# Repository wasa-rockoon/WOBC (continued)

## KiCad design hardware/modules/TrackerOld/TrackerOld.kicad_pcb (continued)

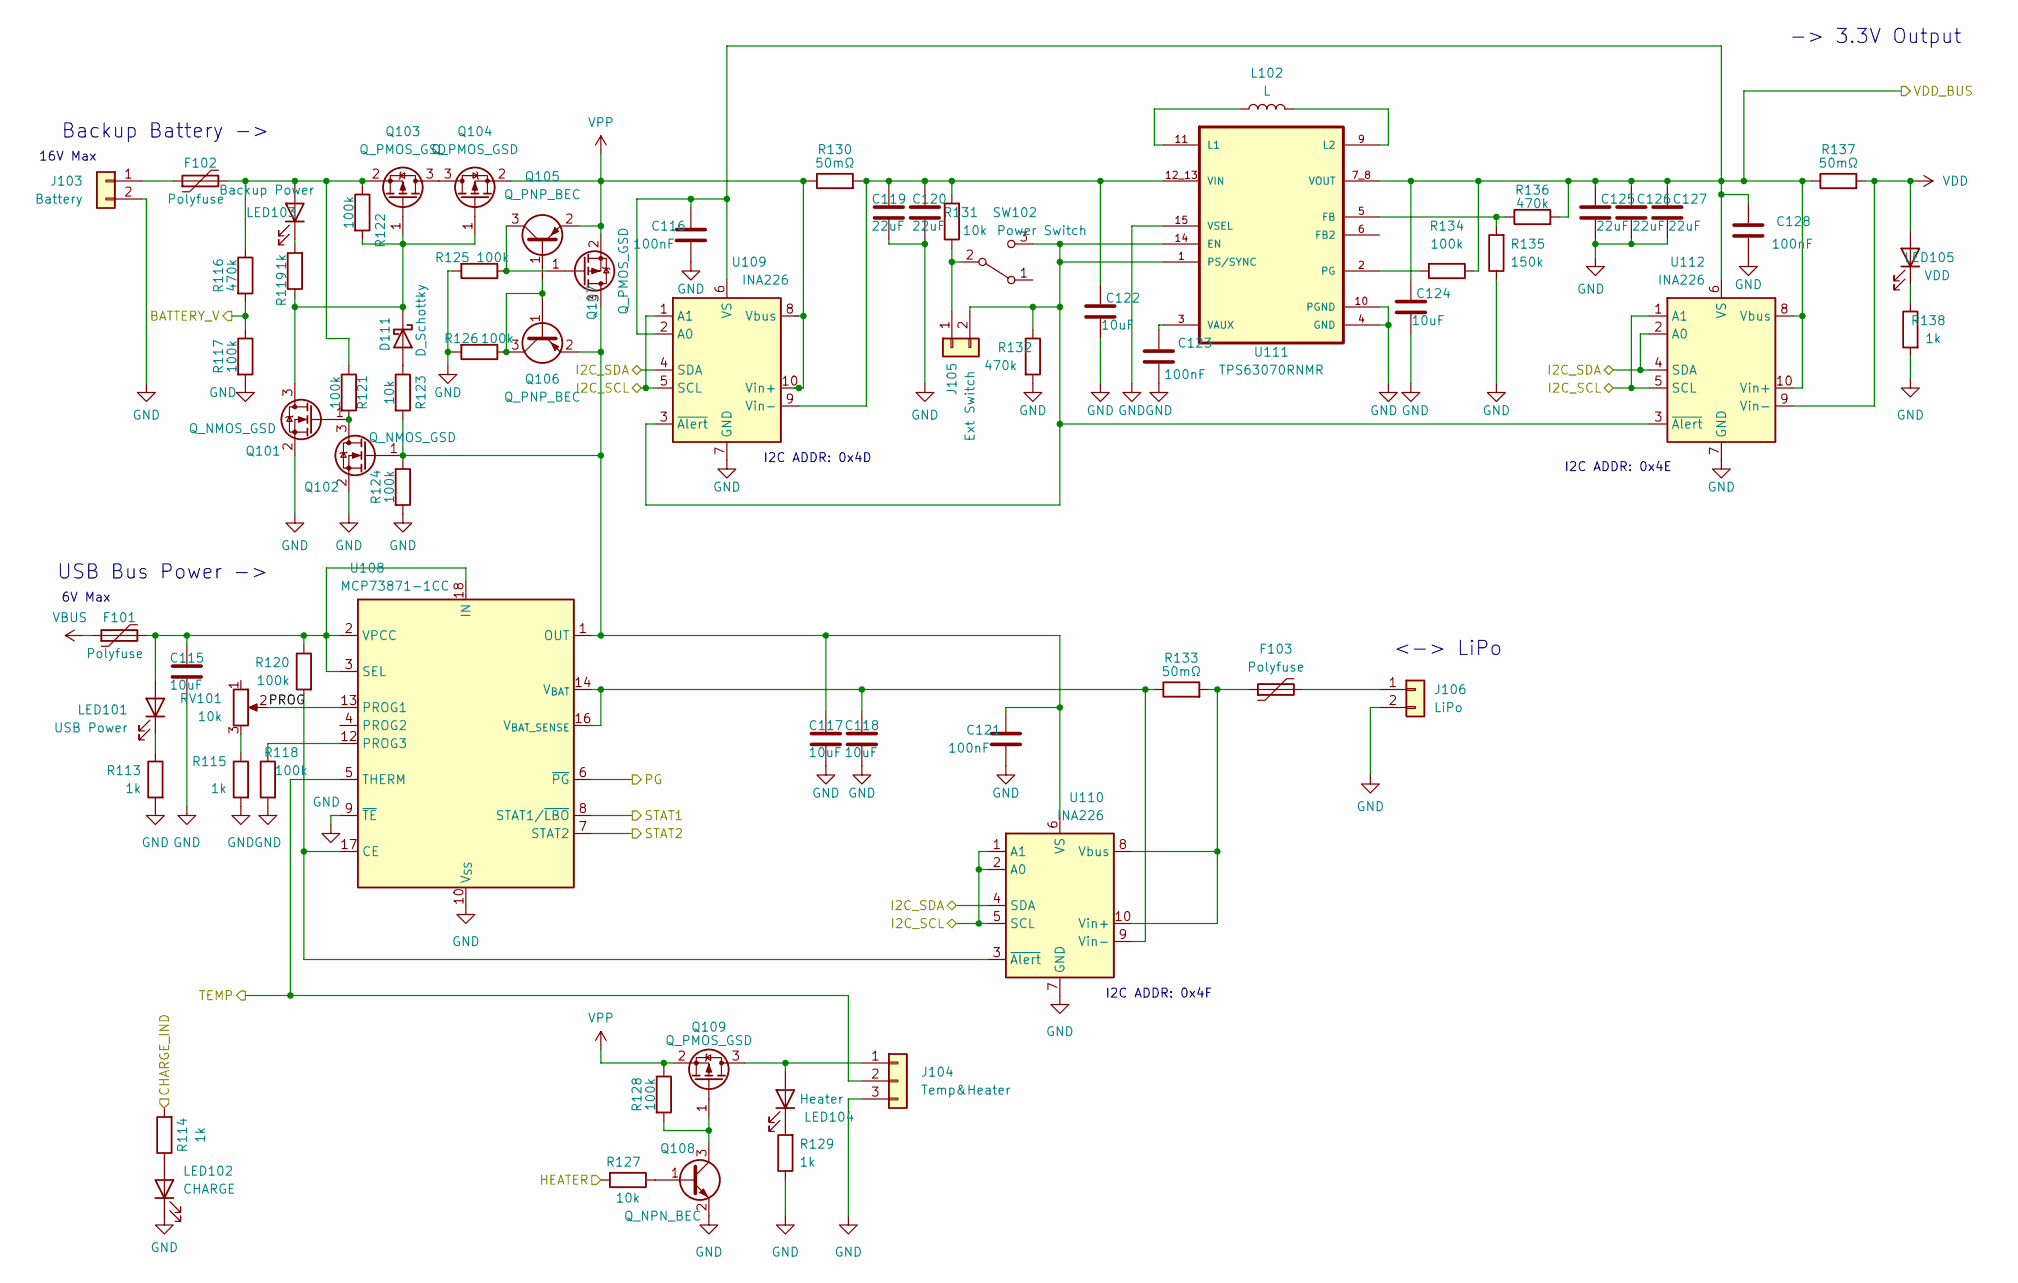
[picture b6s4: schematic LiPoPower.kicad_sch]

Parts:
C115, C117, C118, C122, C124: 10uF; C_0603_1608Metric; LCSC C96446
C116, C121, C123, C128: 100nF; C_0402_1005Metric; LCSC C1525
C119, C120, C125, C126, C127: 22uF; C_0805_2012Metric; LCSC C45783
D111: D_Schottky; D_SOD-323; LCSC C191023
F101, F102, F103: Polyfuse; Fuse_1206_3216Metric; LCSC C883133
J103: Battery; JST_XH_B2B-XH-A_1x02_P2.50mm_Vertical
J104: Temp&Heater; JST_PH_B3B-PH-K_1x03_P2.00mm_Vertical
J105: Ext Switch; JST_PH_B2B-PH-K_1x02_P2.00mm_Vertical
J106: LiPo; JST_PH_B2B-PH-K_1x02_P2.00mm_Vertical
L102: L; L_Wuerth_WE-TPC-3816; LCSC C3033018
LED101: USB Power; LED_0603_1608Metric; LCSC C2297
LED102: CHARGE; LED_0603_1608Metric; LCSC C2296
LED103: Backup Power; LED_0603_1608Metric; LCSC C2297
LED104: Heater; LED_0603_1608Metric; LCSC C2296
LED105: VDD; LED_0603_1608Metric; LCSC C2297
Q101, Q102: Q_NMOS_GSD; SOT-23-3; LCSC C20917
Q103, Q104, Q107, Q109: Q_PMOS_GSD; SOT-23; LCSC C15127
Q105, Q106: Q_PNP_BEC; SOT-23-3; LCSC C8326
Q108: Q_NPN_BEC; SOT-23; LCSC C20526
R113, R114, R115, R119, R129, R138: 1k; R_0402_1005Metric; LCSC C11702
R116, R132, R136: 470k; R_0402_1005Metric; LCSC C25790
R117, R118, R120, R121, R122, R124, R125, R126, R128, R134: 100k; R_0402_1005Metric; LCSC C25530
R123, R127, R131: 10k; R_0402_1005Metric; LCSC C25744
R130, R133, R137: 50mΩ; R_0805_2012Metric; LCSC C247588
R135: 150k; R_0402_1005Metric; LCSC C25755
RV101: 10k; Potentiometer_Bourns_TC33X_Vertical; LCSC C719176
SW102: Power Switch; SW_Slide_SPDT_Angled_CK_OS102011MA1Q
U108: MCP73871-1CC; QFN-20-1EP_4x4mm_P0.5mm_EP2.5x2.5mm; LCSC C511310
U109, U110, U112: INA226; VSSOP-10_3x3mm_P0.5mm; LCSC C49851
U111: TPS63070RNMR; VREG_TPS63070RNMR; LCSC C109322

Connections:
/ESP32/CANH: U108.7 (STAT2); also elsewhere on the board
/ESP32/CANL: U108.8 (STAT1/~LBO); also elsewhere on the board
/ESP32/GPIO6/ADC1_CH5: R116.2, R117.1; also elsewhere on the board
/ESP32/GPIO7/ADC1_CH6: J104.2, U108.5 (THERM); also elsewhere on the board
/ESP32/GPIO8/ADC1_CH7: R114.2; also elsewhere on the board
/ESP32/GPIO9/ADC1_CH8: R127.2; also elsewhere on the board
/ESP32/GPIO10/ADC1_CH9: U108.6 (~PG); also elsewhere on the board
/ESP32/I2C_SCL: U109.1 (A1), U109.5 (SCL), U110.1 (A1), U110.2 (A0), U110.5 (SCL), U112.1 (A1), U112.5 (SCL); also elsewhere on the board
/ESP32/I2C_SDA: U109.4 (SDA), U110.4 (SDA), U112.2 (A0), U112.4 (SDA); also elsewhere on the board
/Lipo/PROG: RV101.2, U108.13 (PROG1)
/Lipo/VDD_BUS: C116.1, C124.1, C125.1, C126.1, C127.1, C128.1, R134.1, R136.2, R137.1, U109.2 (A0), U109.6 (VS), U111.7_8 (VOUT), U112.6 (VS), U112.8 (Vbus), U112.10 (Vin+)
GND: C115.2, C116.2, C117.2, C118.2, C119.2, C120.2, C121.2, C122.2, C123.2, C124.2, C125.2, C126.2, C127.2, C128.2, J103.2, J104.3, J106.2, LED102.1 (K), Q101.2 (S), Q102.2 (S), Q108.2 (E), R113.2, R115.2, R117.2, R118.2, R124.2, R125.2, R126.2, R129.1, R132.2, R135.1, R138.2, U108.9 (~TE), U108.10 (V_{SS}), U108.11 (V_{SS}), U108.21 (V_{SS}), U109.7 (GND), U110.7 (GND), U111.4 (GND), U111.10 (PGND), U111.15 (VSEL), U112.7 (GND); also elsewhere on the board
unnamed: D111.2 (A), R123.1
unnamed: D111.1 (K), Q101.3 (D), Q103.1 (G), Q104.1 (G), R119.1, R122.2
unnamed: F102.1, J103.1
unnamed: J104.1, LED104.2 (A), Q109.3 (D)
unnamed: J105.1, R131.1, SW102.2 (B)
unnamed: J105.2, R132.1, SW102.3 (C), U109.3 (~Alert), U111.1 (PS/SYNC), U111.14 (EN), U112.3 (~Alert)
unnamed: F103.2, J106.1
unnamed: C115.1, F101.2, LED101.2 (A), R120.1, U108.2 (VPCC), U108.3 (SEL), U108.18 (IN), U108.19 (IN)
unnamed: LED101.1 (K), R113.1
unnamed: LED102.2 (A), R114.1
unnamed: F102.2, LED103.2 (A), Q103.2 (S), R116.1, R121.1, R122.1
unnamed: LED103.1 (K), R119.2
unnamed: LED104.1 (K), R129.2
unnamed: LED105.1 (K), R138.1
unnamed: Q101.1 (G), Q102.3 (D), R121.2
unnamed: C117.1, C121.1, Q102.1 (G), Q106.2 (E), Q107.3 (D), R123.2, R124.1, U108.1 (OUT), U108.20 (OUT), U110.6 (VS)
unnamed: Q103.3 (D), Q104.3 (D)
unnamed: Q105.1 (B), Q106.1 (B), Q106.3 (C), R126.1
unnamed: Q105.3 (C), Q107.1 (G), R125.1
unnamed: Q108.1 (B), R127.1
unnamed: Q108.3 (C), Q109.1 (G), R128.2
unnamed: R115.1, RV101.3
unnamed: R120.2, U108.17 (CE), U110.3 (~Alert)
unnamed: R118.1, U108.12 (PROG3)
unnamed: C118.1, R133.1, U108.14 (V_{BAT}), U108.15 (V_{BAT}), U108.16 (V_{BAT_SENSE}), U110.9 (Vin-)
unnamed: C119.1, C120.1, C122.1, R130.2, R131.2, U109.9 (Vin-), U111.12_13 (VIN)
unnamed: F103.1, R133.2, U110.8 (Vbus), U110.10 (Vin+)
unnamed: R135.2, R136.1, U111.5 (FB)
unnamed: L102.1, U111.11 (L1)
unnamed: L102.2, U111.9 (L2)
unnamed: R134.2, U111.2 (PG)
unnamed: C123.1, U111.3 (VAUX)
VBUS: F101.1
VDD: LED105.2 (A), R137.2, U112.9 (Vin-); also elsewhere on the board
VPP: Q104.2 (S), Q105.2 (E), Q107.2 (S), Q109.2 (S), R128.1, R130.1, U109.10 (Vin+)

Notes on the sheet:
6V Max
USB Bus Power ->
<-> LiPo
I2C ADDR: 0x4D
I2C ADDR: 0x4F
-> 3.3V Output
16V Max
I2C ADDR: 0x4E
Backup Battery ->

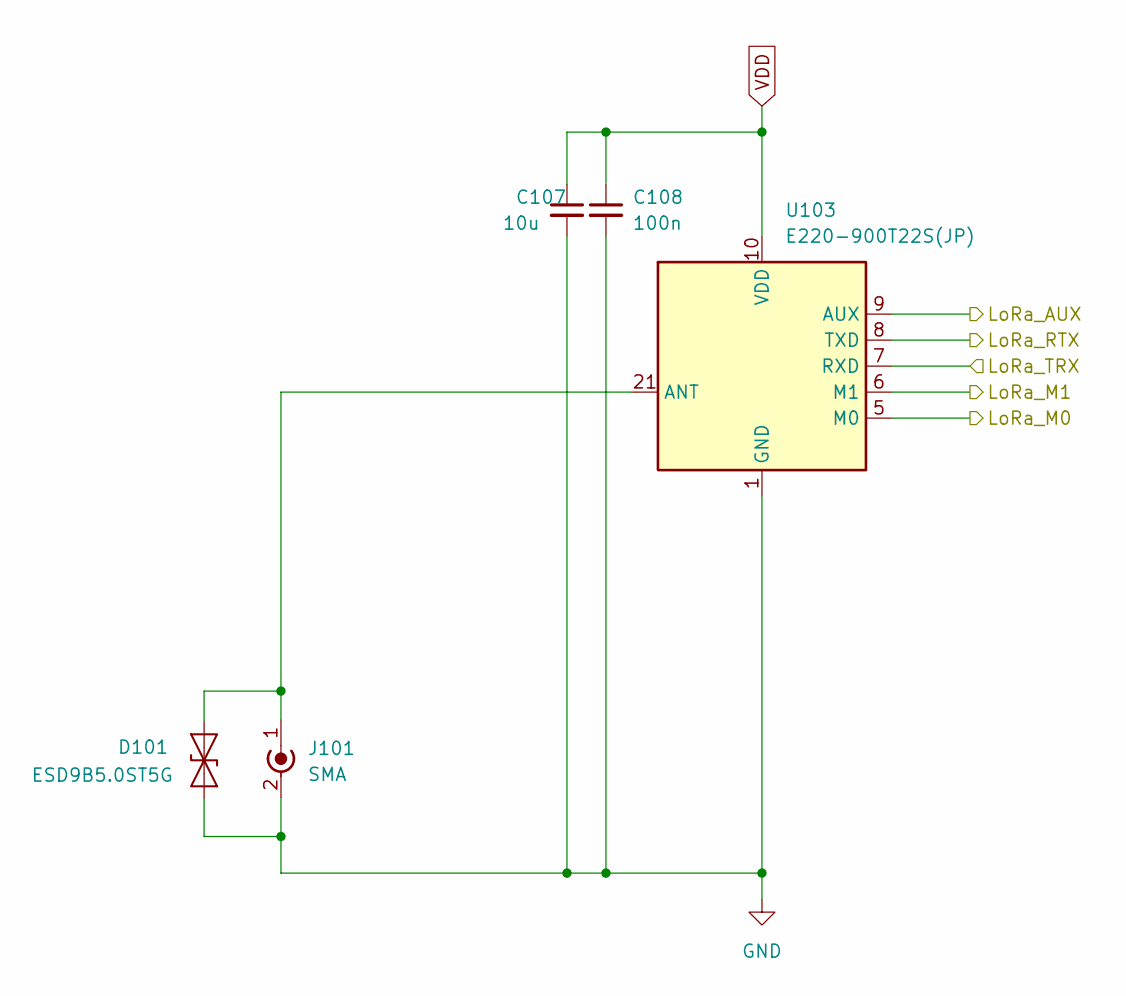
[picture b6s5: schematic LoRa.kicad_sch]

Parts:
C107: 10u; C_0603_1608Metric; LCSC C96446
C108: 100n; C_0402_1005Metric; LCSC C1525
D101: ESD9B5.0ST5G; D_SOD-882; LCSC C7420372
J101: SMA; SMA_Amphenol_132203-12_Horizontal; LCSC C2693813
U103: E220-900T22S(JP)

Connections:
/ESP32/GPIO11: U103.6 (M1); also elsewhere on the board
/ESP32/GPIO12: U103.5 (M0); also elsewhere on the board
/ESP32/GPIO38: U103.7 (RXD); also elsewhere on the board
/ESP32/GPIO39: U103.8 (TXD); also elsewhere on the board
/ESP32/GPIO40: U103.9 (AUX); also elsewhere on the board
GND: C107.2, C108.2, D101.1 (A1), J101.2 (Ext), U103.1 (GND), U103.2 (GND), U103.3 (GND), U103.4 (GND), U103.11 (GND), U103.13 (GND), U103.19 (GND), U103.20 (GND), U103.22 (GND); also elsewhere on the board
unnamed: D101.2 (A2), J101.1 (In), U103.21 (ANT)
VDD: C107.1, C108.1, U103.10 (VDD); also elsewhere on the board

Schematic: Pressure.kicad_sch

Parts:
C101, C104: 10μF; C_0603_1608Metric; LCSC C96446
C102, C103: 100nF; C_0402_1005Metric; LCSC C1525
U101: BME280; LCSC C92489

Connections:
/ESP32/I2C_SCL: U101.4 (SCK); also elsewhere on the board
/ESP32/I2C_SDA: U101.3 (SDI); also elsewhere on the board
GND: C101.2, C102.2, C103.2, C104.2, U101.1 (GND), U101.5 (SDO), U101.7 (GND); also elsewhere on the board
VDD: C101.1, C102.1, C103.1, C104.1, U101.2 (CSB), U101.6 (VDDIO), U101.8 (VDD); also elsewhere on the board

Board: 2 copper layers, 122 parts (28 on the bottom side), 91 nets, no tracks yet.

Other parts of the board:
Switch101: XA17-G4K1; SOT-363_SC-70-6

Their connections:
/ESP32/GPIO13: Switch101.4 (V1); also elsewhere on the board
/ESP32/GPIO14: Switch101.6 (V2); also elsewhere on the board
GND: Switch101.2 (GND); also elsewhere on the board

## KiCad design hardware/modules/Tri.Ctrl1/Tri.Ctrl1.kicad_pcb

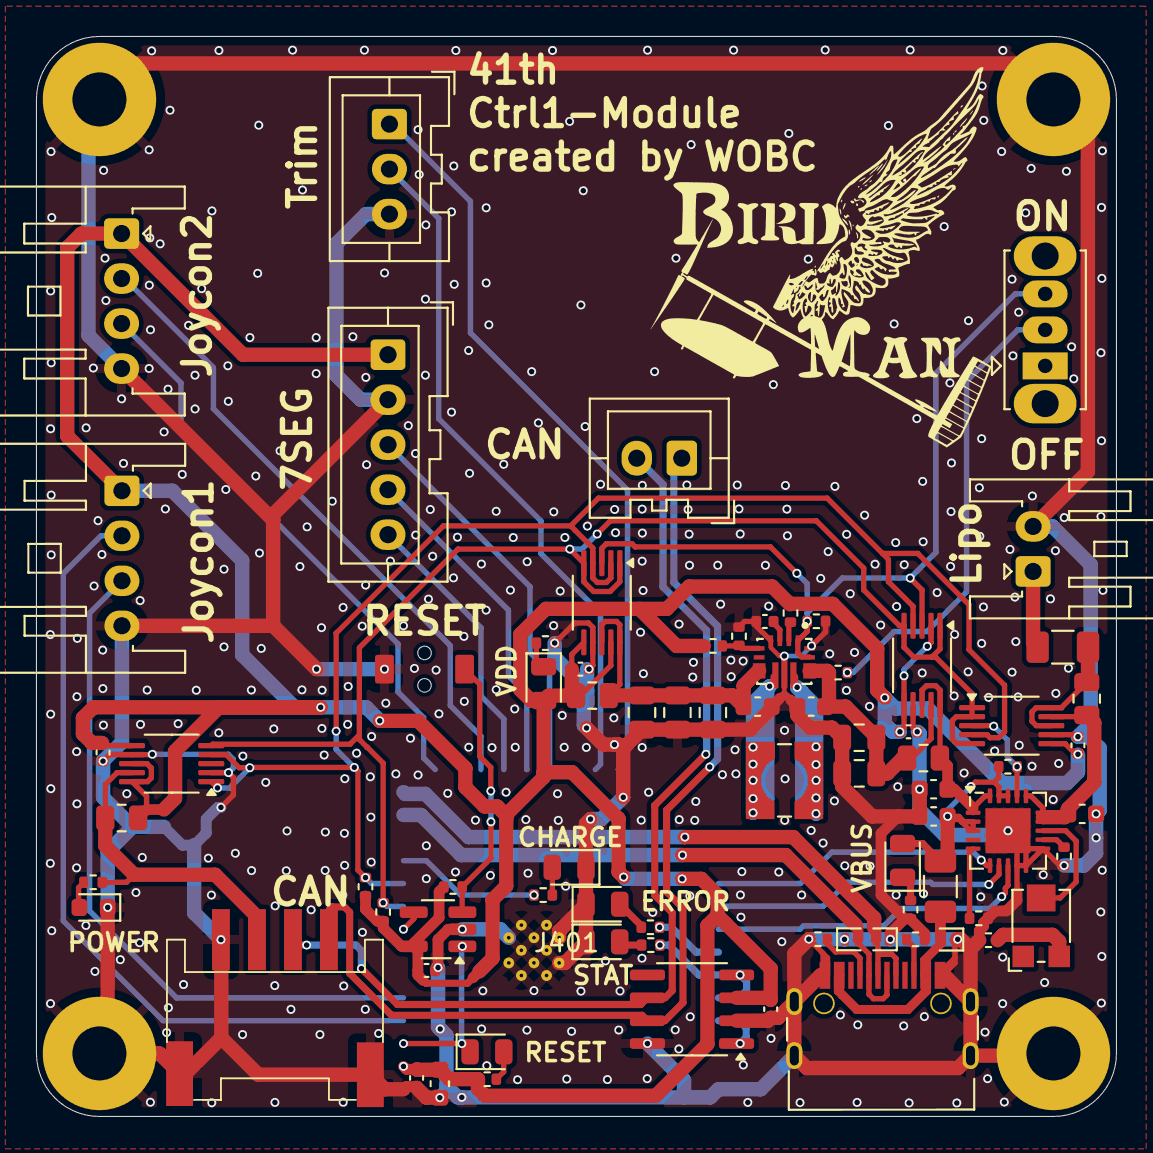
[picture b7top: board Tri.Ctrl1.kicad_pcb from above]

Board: 2 copper layers, 60.0 x 60.0 mm, 78 parts (1 on the bottom side), 57 nets.

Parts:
B101: Board_1U_60x60
C201, C202, C204, C301, C502, C507, C509, C514: 100nF; C_0402_1005Metric
C203, C501, C503, C504, C508, C510: 10uF; C_0603_1608Metric
C505, C506, C511, C512, C513: 22uF; C_0805_2012Metric
D201, D202, D203: 5V; D_SOD-882
D204: RESET; LED_0805_2012Metric
D205: ERROR; LED_0805_2012Metric
D206: STAT; LED_0805_2012Metric
F501, F502: Polyfuse; Fuse_1206_3216Metric
J101: ジョイコン1; JST_XA_S04B-XASK-1N-BN_1x04_P2.50mm_Horizontal
J102: ジョイコン2; JST_XA_S04B-XASK-1N-BN_1x04_P2.50mm_Horizontal
J103: 7セグ; JST_XA_B05B-XASK-1_1x05_P2.50mm_Vertical
J104: トリム; JST_XA_B03B-XASK-1_1x03_P2.50mm_Vertical
J301: Conn_01x04_MountingPin; Grove_4P_L_SMD
J401: Conn_01x02_Pin; JST_XA_B02B-XASK-1_1x02_P2.50mm_Vertical
J501: LiPo; JST_XA_S02B-XASK-1N-BN_1x02_P2.50mm_Horizontal
L501: L; L_Wuerth_WE-TPC-3816
LED301: Power; LED_0603_1608Metric
LED501: USB Power; LED_0805_2012Metric
LED502: CHARGE; LED_0805_2012Metric
LED503: VDD; LED_0805_2012Metric
R201, R206, R208, R505, R508: 10k; R_0402_1005Metric
R202, R203: 5.1k; R_0402_1005Metric
R204, R205, R207: 470; R_0402_1005Metric
R301, R507, R510, R514: 50mΩ; R_0805_2012Metric
R302, R501, R502, R503, R515: 1k; R_0402_1005Metric
R504, R506, R511: 100k; R_0402_1005Metric
R509: 330k; R_0402_1005Metric
R512: 15k; R_0402_1005Metric
R513: 47k; R_0402_1005Metric
RV501: 10k; Potentiometer_Bourns_TC33X_Vertical
SW201: RESET_sw; TVAF06-A020B-R
SW501: Power Switch; SW_Slide_SPDT_Straight_CK_OS102011MS2Q
U201: TPS3820; SOT-23-5_HandSoldering
U202: SN65HVD230; SOIC-8_3.9x4.9mm_P1.27mm
U203: ESP32-S3-WROOM-1
U301, U502, U503, U505: INA226; VSSOP-10_3x3mm_P0.5mm
U501: MCP73871-1CC; QFN-20-1EP_4x4mm_P0.5mm_EP2.5x2.5mm
U504: TPS63070RNMR; VREG_TPS63070RNMR
USB201: USB_C_Receptacle_USB2.0; USB_C_TYPEC-301S-ACP16X7

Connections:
/CANH: J301.1, J401.1, U202.7 (CANH)
/CANL: J301.2, J401.2, U202.6 (CANL)
/DOWN: J104.2, U203.22 (GPIO14/TOUCH14/ADC2_CH3/FSPIWP/FSPIDQS/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)
/ESP32Core/CAN_RX: U202.4 (R), U203.36 (U0RXD/GPIO44/CLK_OUT2)
/ESP32Core/CAN_TX: U202.1 (D), U203.37 (U0TXD/GPIO43/CLK_OUT1)
/ESP32Core/GPIO3/ADC1_CH2: J102.3, U203.15 (GPIO3/TOUCH3/ADC1_CH2)
/ESP32Core/GPIO4/ADC1_CH3: J101.2, U203.4 (GPIO4/TOUCH4/ADC1_CH3)
/ESP32Core/GPIO5/ADC1_CH4: J101.3, U203.5 (GPIO5/TOUCH5/ADC1_CH4)
/ESP32Core/GPIO9/ADC1_CH8: J102.2, U203.17 (GPIO9/TOUCH9/ADC1_CH8/FSPIHD/SUBSPIHD)
/ESP32Core/GPIO18: R502.2, U203.11 (GPIO18/U1RXD/ADC2_CH7/CLK_OUT3)
/ESP32Core/USB_D+: D202.2 (A2), U203.14 (GPIO20/U1CTS/ADC2_CH9/CLK_OUT1/USB_D+), USB201.A6 (D+), USB201.B6 (D+)
/ESP32Core/USB_D-: D203.2 (A2), U203.13 (GPIO19/U1RTS/ADC2_CH8/CLK_OUT2/USB_D-), USB201.A7 (D-), USB201.B7 (D-)
/ESP32Core/WDI: U201.4 (WDI), U203.8 (GPIO15/U0RTS/ADC2_CH4/XTAL_32K_P)
/LATCH: J103.5, U203.18 (GPIO10/TOUCH10/ADC1_CH9/FSPICS0/FSPIIO4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)
/PG: U203.31 (GPIO38/FSPIWP/SUBSPIWP), U501.6 (~PG)
/Power/PROG: RV501.2, U501.13 (PROG1)
/SCK: J103.4, U203.19 (GPIO11/TOUCH11/ADC2_CH0/FSPID/FSPIIO5/S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)
/SCL: R206.2, U203.9 (GPIO16/U0CTS/ADC2_CH5/XTAL_32K_N), U301.5 (SCL), U502.1 (A1), U502.5 (SCL), U503.1 (A1), U503.2 (A0), U503.5 (SCL), U505.1 (A1), U505.5 (SCL)
/SDA: R208.2, U203.10 (GPIO17/U1TXD/ADC2_CH6), U301.1 (A1), U301.4 (SDA), U502.4 (SDA), U503.4 (SDA), U505.2 (A0), U505.4 (SDA)
/SDI: J103.3, U203.20 (GPIO12/TOUCH12/ADC2_CH1/FSPICLK/FSPIIO6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)
/STAT1: U203.33 (MTDO/GPIO40/CLK_OUT2), U501.8 (STAT1/~LBO)
/STAT2: U203.32 (MTCK/GPIO39/CLK_OUT3/SUBSPICS1), U501.7 (STAT2)
/UP: J104.1, U203.23 (GPIO21)
GND: B101.GND, C201.1, C202.1, C203.1, C204.2, C301.1, C501.2, C502.2, C503.2, C504.2, C505.2, C506.2, C507.2, C508.2, C509.2, C510.2, C511.2, C512.2, C513.2, C514.2, D201.1 (A1), D202.1 (A1), D203.1 (A1), D205.1 (K), D206.1 (K), J101.4, J102.4, J103.2, J104.3, J301.4, J301.MP (MountPin), J501.2, LED301.1 (K), LED502.1 (K), R202.2, R203.2, R501.2, R503.2, R504.2, R505.2, R509.2, R512.1, R515.2, SW201.2, U201.2 (GND), U202.2 (GND), U202.8 (Rs), U203.1 (GND), U203.40 (GND), U203.41 (GND), U301.2 (A0), U301.7 (GND), U501.9 (~TE), U501.10 (V_{SS}), U501.11 (V_{SS}), U501.21 (V_{SS}), U502.7 (GND), U503.7 (GND), U504.4 (GND), U504.10 (PGND), U504.15 (VSEL), U505.7 (GND), USB201.A1 (GND), USB201.A12 (GND), USB201.B1 (GND), USB201.B12 (GND), USB201.S1 (SHIELD)
unnamed: D204.2 (A), R204.2
unnamed: D205.2 (A), R205.2
unnamed: D206.2 (A), R207.2
unnamed: J301.3, R301.2, R302.2, U301.9 (Vin-)
unnamed: F502.2, J501.1
unnamed: LED301.2 (A), R302.1
unnamed: C501.1, F501.2, LED501.2 (A), R506.1, U501.2 (VPCC), U501.3 (SEL), U501.18 (IN), U501.19 (IN)
unnamed: LED501.1 (K), R501.1
unnamed: LED502.2 (A), R502.1
unnamed: LED503.1 (K), R515.1
unnamed: R503.1, RV501.3
unnamed: R508.1, SW501.2 (B)
unnamed: R509.1, SW501.3 (C), U502.3 (~Alert), U504.1 (PS/SYNC), U504.14 (EN), U505.3 (~Alert)
unnamed: R201.2, SW201.1, U201.3 (MR)
unnamed: R205.1, U203.34 (MTDI/GPIO41/CLK_OUT1)
unnamed: R207.1, U203.35 (MTMS/GPIO42)
unnamed: R506.2, U501.17 (CE), U503.3 (~Alert)
unnamed: R504.1, U501.12 (PROG3)
unnamed: R505.1, U501.5 (THERM)
unnamed: C504.1, R510.1, U501.14 (V_{BAT}), U501.15 (V_{BAT}), U501.16 (V_{BAT_SENSE}), U503.9 (Vin-)
unnamed: C505.1, C506.1, C508.1, R507.2, R508.2, U502.9 (Vin-), U504.12_13 (VIN)
unnamed: F502.1, R510.2, U503.8 (Vbus), U503.10 (Vin+)
unnamed: R512.2, R513.1, U504.5 (FB)
unnamed: L501.1, U504.11 (L1)
unnamed: L501.2, U504.9 (L2)
unnamed: R511.2, U504.2 (PG)
unnamed: C509.1, U504.3 (VAUX)
unnamed: R202.1, USB201.A5 (CC1)
unnamed: R203.1, USB201.B5 (CC2)
RESET: D204.1 (K), U201.1 (RESET), U203.3 (EN)
VBUS: D201.2 (A2), F501.1, USB201.A4 (VBUS), USB201.A9 (VBUS), USB201.B4 (VBUS), USB201.B9 (VBUS)
VDD: C201.2, C202.2, C203.2, C204.1, C301.2, C502.1, C507.1, C510.1, C511.1, C512.1, C513.1, C514.1, J101.1, J102.1, J103.1, LED503.2 (A), R201.1, R204.1, R206.1, R208.1, R301.1, R511.1, R513.2, R514.1, R514.2, U201.5 (VDD), U202.3 (VCC), U203.2 (3V3), U301.6 (VS), U301.8 (Vbus), U301.10 (Vin+), U502.2 (A0), U502.6 (VS), U503.6 (VS), U504.7_8 (VOUT), U505.6 (VS), U505.8 (Vbus), U505.9 (Vin-), U505.10 (Vin+)
VPP: C503.1, R507.1, U501.1 (OUT), U501.20 (OUT), U502.8 (Vbus), U502.10 (Vin+)
